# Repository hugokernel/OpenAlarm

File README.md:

OpenAlarm
=========

Un système d'alarme libre.

Caractéristiques :

- Uniquement basé sur des briques libres (OpenSource / OpenHardware)
- Autonomie très grande des modules capteurs, appelés « Node » (plusieurs mois)
- Les Node sont basés sur un µcontrolleur Atmel AVR ATMega32U4 et l'interface radio, sur un RFM12B (basé sur un Si4421 http://www.silabs.com/products/wireless/EZRadio/Pages/Si442021.aspx)
- Programmation et recharge simple des Node par USB (port µUSB inclu)
- Pas besoin de base : 2 Node suffisent à faire fonctionner une surveillance
- Possibilité de modifier les paramètres d'un Node à distance
- Technos utilisées : Arduino (Ino) pour les Node, et Python pour l'interface avec un PC
- Les entrées / sorties sont facilement accessible (au pas de 2.54mm)
- 2 leds (vertes et rouges) inclues sur chaque Node

Les premiers Node sont fonctionnel en version 1.5.0, les schémas de principe et PCB sont disponible en PDF dans le dossier https://github.com/hugokernel/OpenAlarm/blob/master/hardware/export/pdf/node/1.5.0/

Pour rester informer, ça se passe sur le site officiel d'OpenAlarm http://openalarm.net/, vous pouvez venir en parler sur le canal irc #madeinfr sur le réseau freenode.

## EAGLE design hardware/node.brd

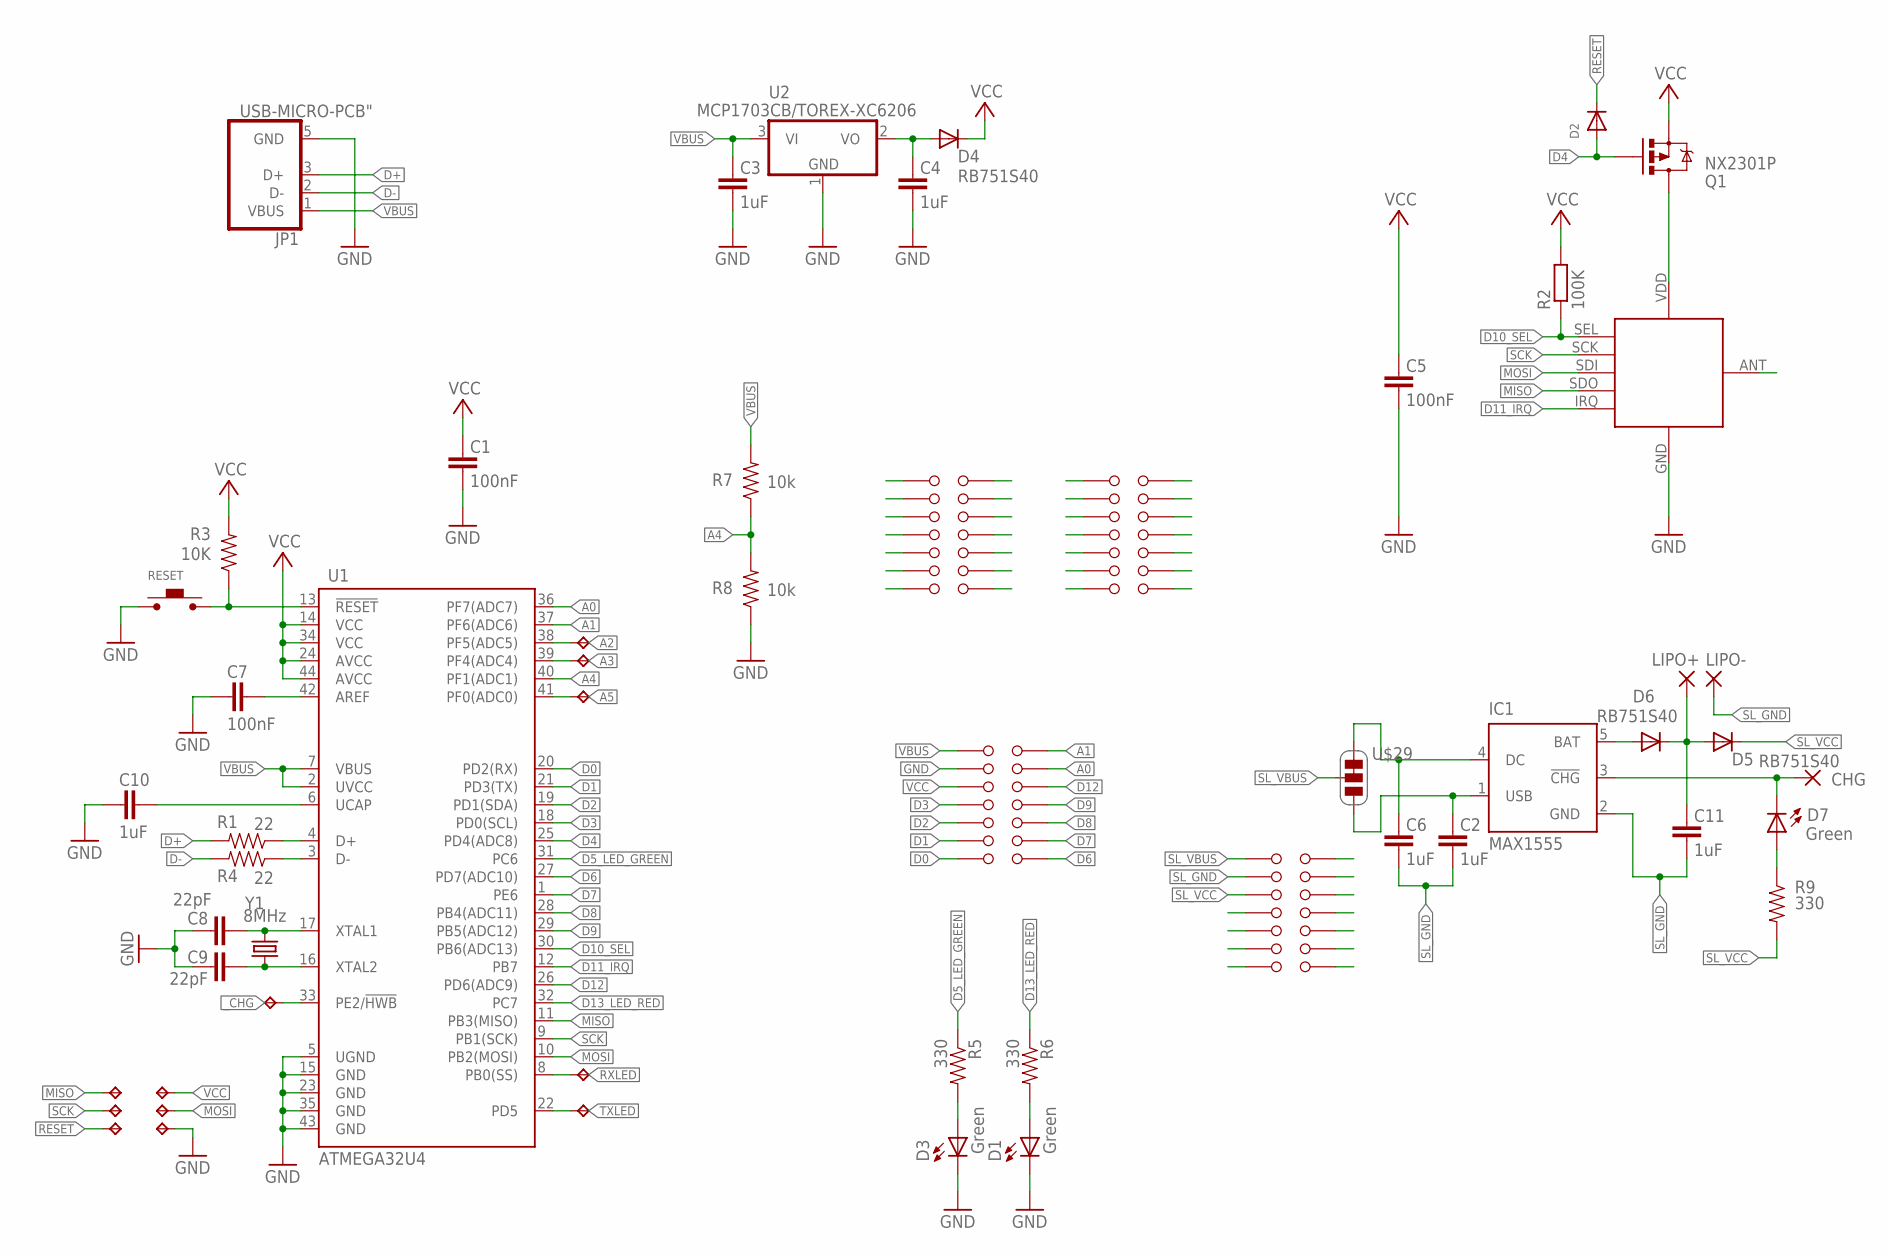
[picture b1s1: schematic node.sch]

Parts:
C1, C5, C7: 100nF; 0402-CAP
C2, C3, C4, C6, C10, C11: 1uF; 0402-CAP
C8, C9: 22pF; 0402-CAP
CHG: WIREPAD1,6/0,8; 1,6/0,8
D1, D3, D7: Green; LED-0603
D2: DIODESOD-323F; SOD-323F
D4, D5, D6: RB751S40; SOD523
IC1: MAX1555; SOT23-5L
JP1: USB-MICRO-PCB"; USB-MICRO-PCB
LIPO+: WIREPAD1,6/0,8; 1,6/0,8
LIPO-: WIREPAD1,6/0,8; 1,6/0,8
Q1: NX2301P; SOT23
R1, R4: 22; 0402-RES
R2: 100K; R0402
R3: 10K; 0402-RES
R5, R6, R9: 330; 0402-RES
R7, R8: 10k; 0402-RES
RESET: MICROSWITCH
RFMXX: RFM12B_MINPADS; RFM12B-MINPADS
TP1, TP2, TP3, TP4, TP5, TP14: TPTP13R; TP13R
TP7, TP8, TP9, TP10, TP11, TP12: TPTP08R; TP08R
U1: ATMEGA32U4; QFN-44-NOPAD
U2: MCP1703CB/TOREX-XC6206; SOT23
U$1, U$2, U$3, U$4, U$5, U$6, U$7, U$8, U$9, U$10, U$11, U$12, U$13, U$14, U$15, U$16, U$17, U$18, U$19, U$20, U$21, U$22, U$23, U$24, U$25, U$26, U$27, U$28, U$30, U$31, U$32, U$33, U$34, U$35, U$36, U$37, U$38, U$39, U$40, U$41, U$42, U$43, U$44, U$45, U$46, U$47, U$48, U$49, U$50, U$51, U$52, U$53, U$54, U$55, U$56, U$57: IOPAD
U$29: UJUMPER-SHORT
Y1: 8MHz; CRYSTAL-SMD-5X3

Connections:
A0: U1.36 (PF7(ADC7)), U$9.P$1
A1: U1.37 (PF6(ADC6)), U$8.P$1
A2: TP7.TP, U1.38 (PF5(ADC5))
A3: TP8.TP, U1.39 (PF4(ADC4))
A4: R7.1, R8.2, U1.40 (PF1(ADC1))
A5: TP10.TP, U1.41 (PF0(ADC0))
AREF: C7.2, U1.42 (AREF)
D0: U1.20 (PD2(RX)), U$2.P$1
D1: U1.21 (PD3(TX)), U$1.P$1
D2: U1.19 (PD1(SDA)), U$3.P$1
D3: U1.18 (PD0(SCL)), U$4.P$1
D4: D2.A, Q1.1 (G), U1.25 (PD4(ADC8))
D5_LED_GREEN: R5.1, U1.31 (PC6)
D6: U1.27 (PD7(ADC10)), U$14.P$1
D7: U1.1 (PE6), U$13.P$1
D8: U1.28 (PB4(ADC11)), U$12.P$1
D9: U1.29 (PB5(ADC12)), U$11.P$1
D10_SEL: R2.1, RFMXX.SEL, U1.30 (PB6(ADC13))
D11_IRQ: RFMXX.IRQ, U1.12 (PB7)
D12: U1.26 (PD6(ADC9)), U$10.P$1
D13_LED_RED: R6.1, U1.32 (PC7)
D+: JP1.3 (D+), R1.2
D-: JP1.2 (D-), R4.2
GND: C1.1, C3.1, C4.1, C5.1, C7.1, C8.2, C9.2, C10.1, D1.C, D3.C, JP1.5 (GND), R8.1, RESET.P$1, RFMXX.GND, TP5.TP, U1.5 (UGND), U1.15 (GND), U1.23 (GND), U1.35 (GND), U1.43 (GND), U2.1 (GND), U$6.P$1
MISO: RFMXX.SDO (SDO/MISO), TP14.TP, U1.11 (PB3(MISO))
MOSI: RFMXX.SDI (SDI/MOSI), TP4.TP, U1.10 (PB2(MOSI))
unnamed: C9.1, U1.16 (XTAL2), Y1.1
unnamed: R1.1, U1.4 (D+)
unnamed: C8.1, U1.17 (XTAL1), Y1.3 (2)
unnamed: C10.2, U1.6 (UCAP)
unnamed: D1.A, R6.2
unnamed: R4.1, U1.3 (D-)
unnamed: D3.A, R5.2
unnamed: Q1.3 (D), RFMXX.VDD
unnamed: D7.A, R9.1
unnamed: CHG.1, D7.C, IC1.3 (!CHG)
unnamed: C6.2, IC1.4 (DC), U$29.C0
unnamed: C2.2, IC1.1 (USB), U$29.C1
unnamed: D6.A, IC1.5 (BAT)
unnamed: C11.2, D5.A, D6.C, LIPO+.1
RESET: D2.C, R3.1, RESET.P$2, TP3.TP, U1.13 (!RESET)
RXLED: TP11.TP, U1.8 (PB0(SS))
SCK: RFMXX.SCK, TP2.TP, U1.9 (PB1(SCK))
SL_GND: C2.1, C6.1, C11.1, IC1.2 (GND), LIPO-.1, U$31.P$1
SL_VBUS: U$29.COM, U$30.P$1
SL_VCC: D5.C, R9.2, U$32.P$1
TXLED: TP9.TP, U1.22 (PD5)
VBAT: C4.2, D4.A, U2.2 (VO)
VBUS: C3.2, JP1.1 (VBUS), R7.2, U1.2 (UVCC), U1.7 (VBUS), U2.3 (VI), U$7.P$1
VCC: C1.2, C5.2, D4.C, Q1.2 (S), R2.2, R3.2, TP1.TP, U1.14 (VCC), U1.24 (AVCC), U1.34 (VCC), U1.44 (AVCC), U$5.P$1
_CHG: TP12.TP, U1.33 (PE2/!HWB)

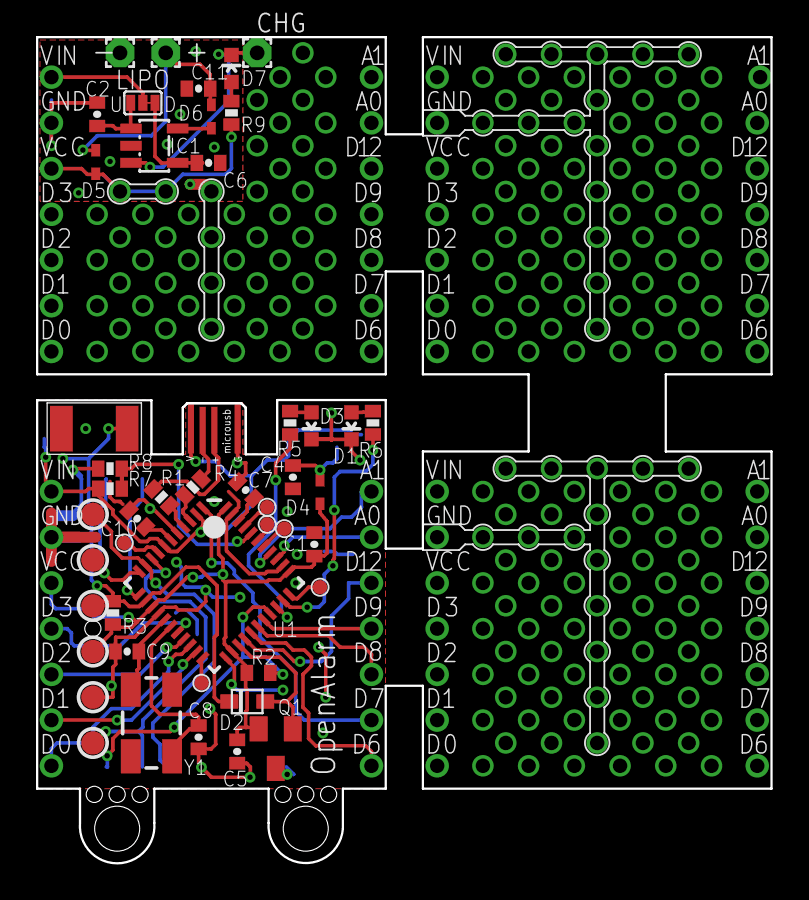
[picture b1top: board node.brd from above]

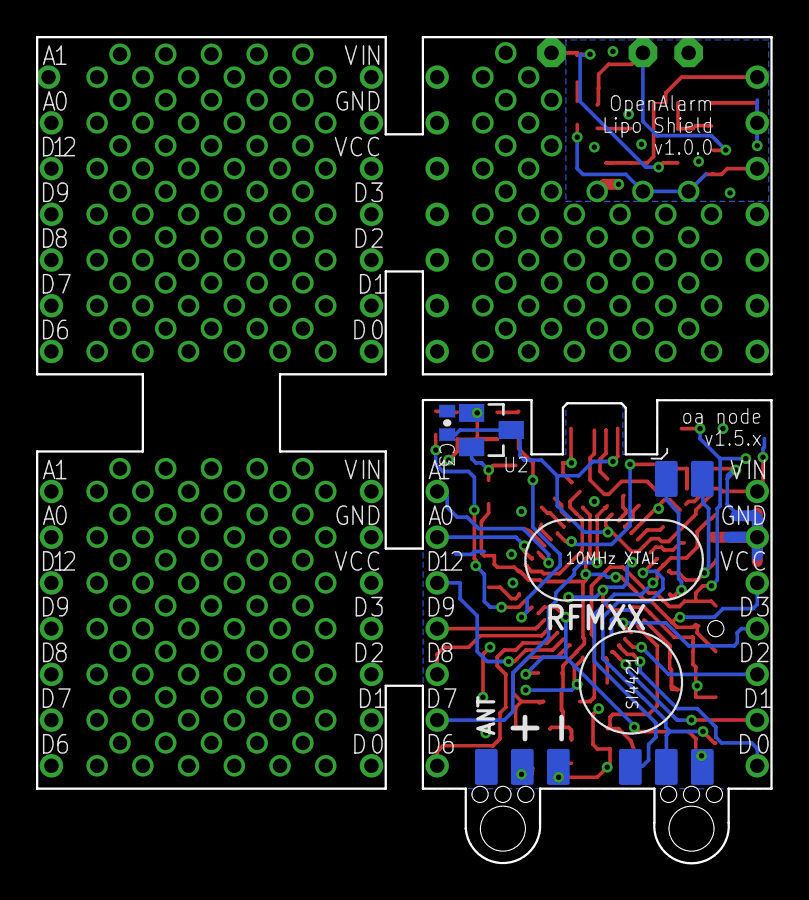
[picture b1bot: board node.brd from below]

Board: 2 copper layers, 40.8 x 45.9 mm, 107 parts (3 on the bottom side), 51 nets.

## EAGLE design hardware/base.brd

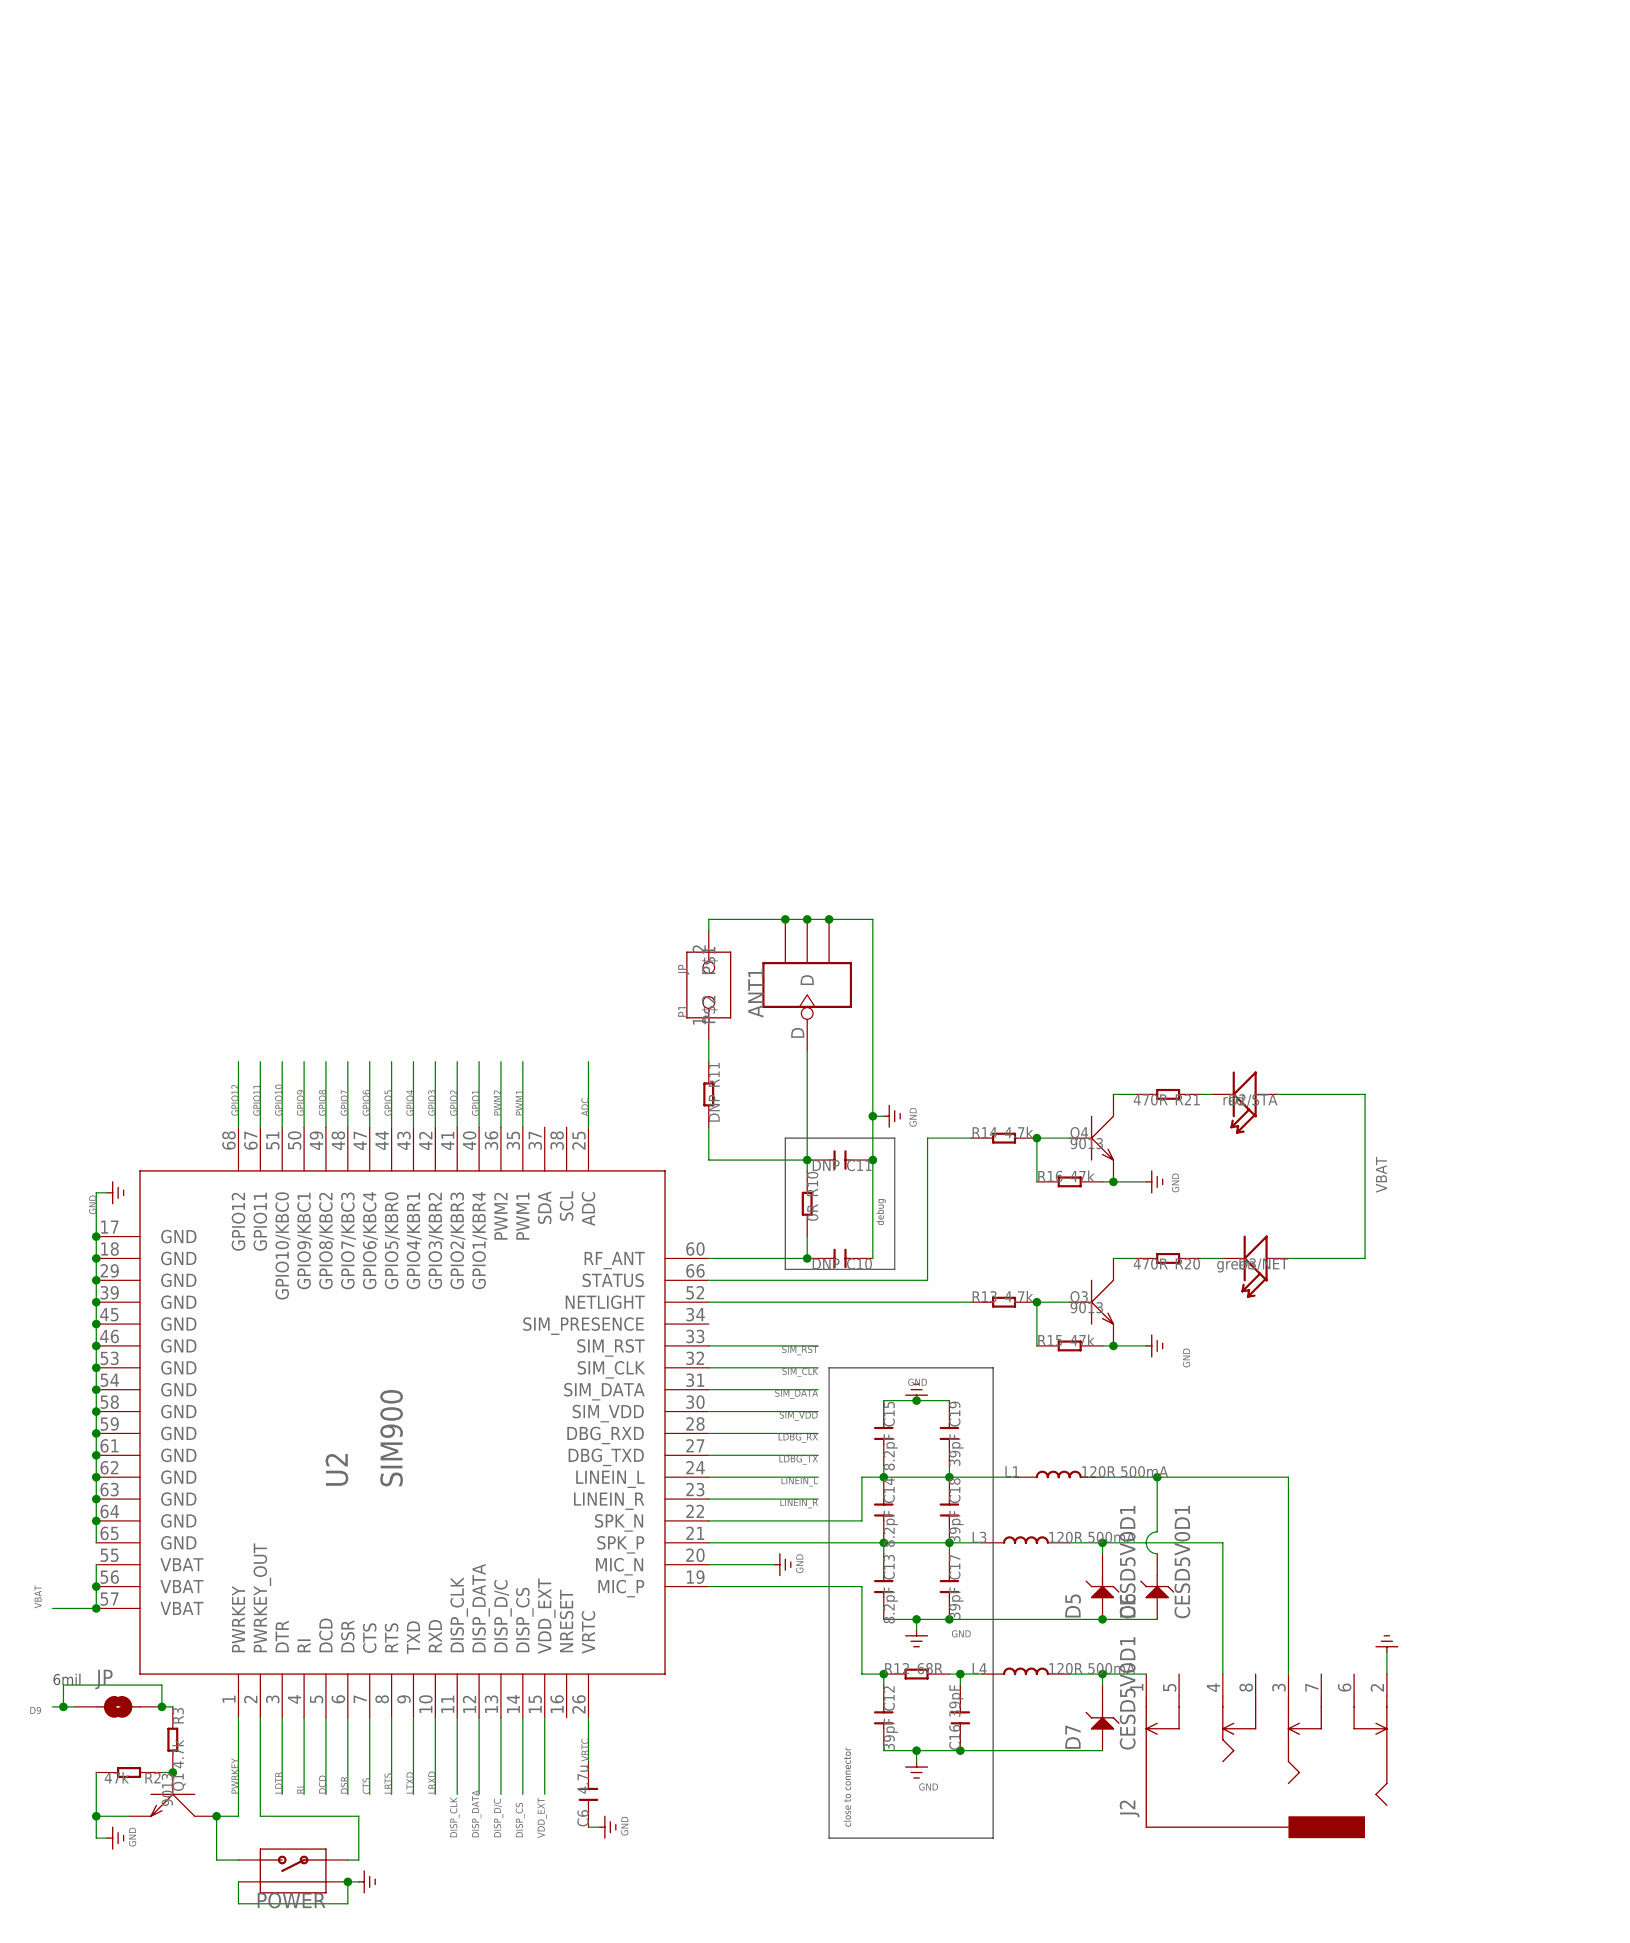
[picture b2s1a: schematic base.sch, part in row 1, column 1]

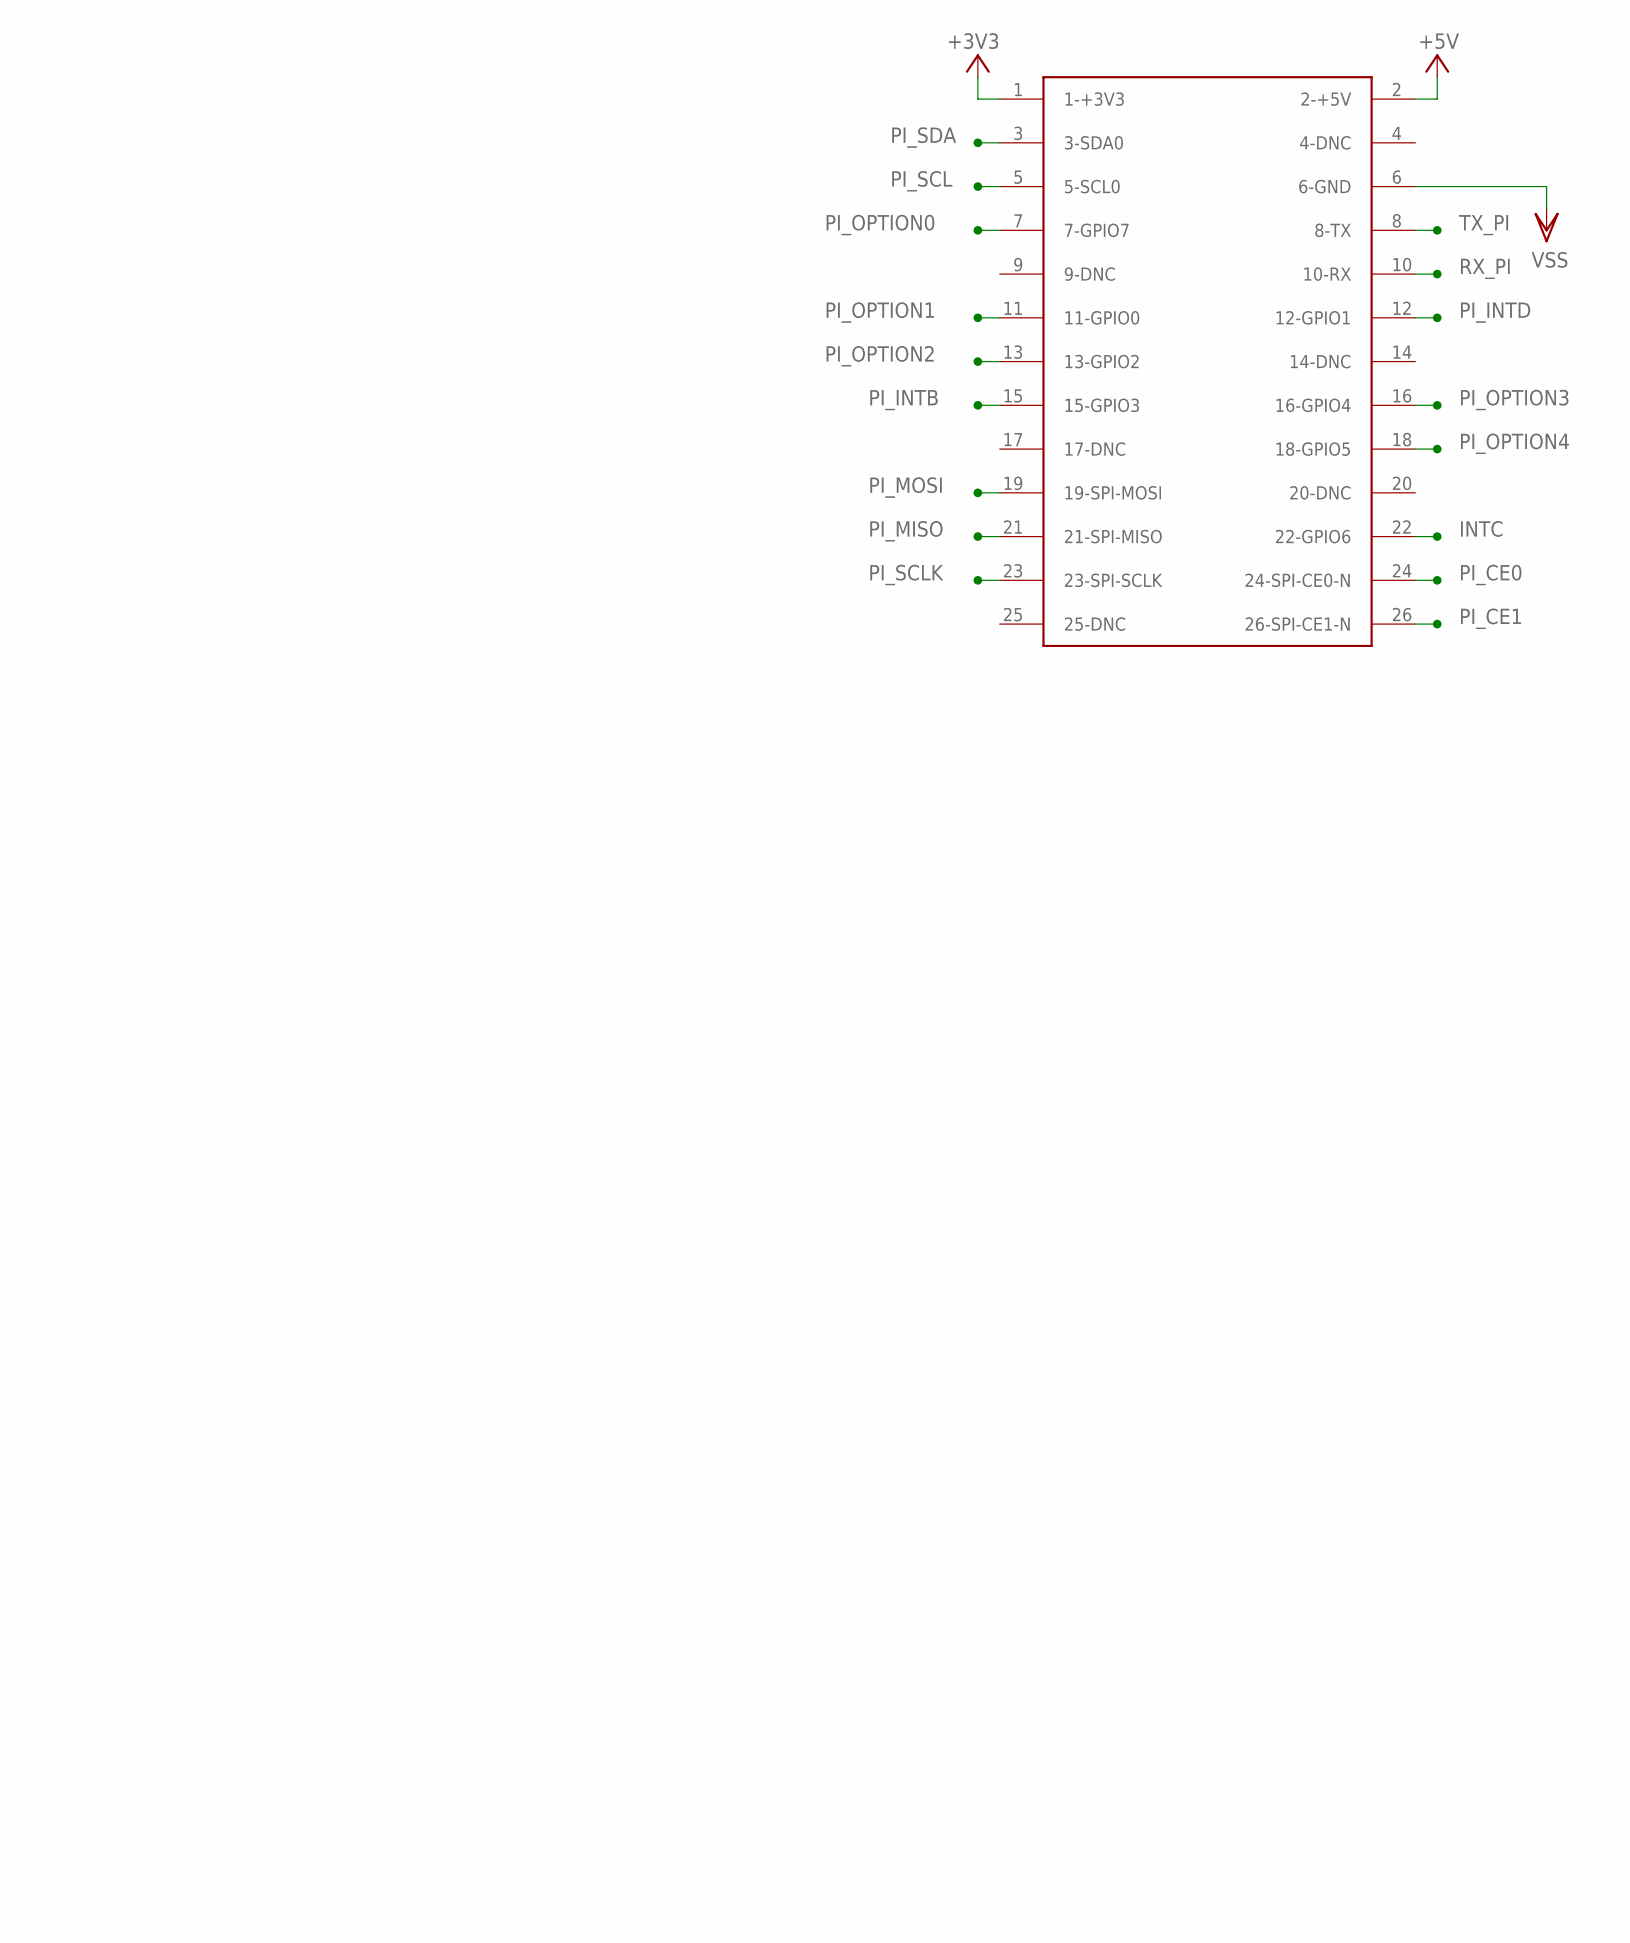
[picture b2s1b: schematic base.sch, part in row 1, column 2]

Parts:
ANT1: ANTENNA-U-FL; 4P-U-FL
C6: 4.7u; C0805
C10, C11: DNP; C0603
C12, C16, C17, C18, C19: 39pF; C0603
C13, C14, C15: 8.2pF; C0603
D2/STA: red; LED-0603
D3/NET: green; LED-0603
D5, D6, D7: CESD5V0D1; SOD123-2.7X1.6
J2: AUDIO-8P'PJ-3536-L6S'; 8P-3.5-SMD
JP: PAD-SOLDERJUMPERNC; 2P-SMD-3.3X2
L1, L3, L4: 120R 500mA; L0603
P1: JP
POWER: BUTTON-4P-REINFORCE'TS-118E'; 4P-SMD-7X3.5X3.5H
Q1, Q3, Q4: 9013; SOT23
R2, R15, R16: 47k; R0603
R3, R13, R14: 4.7k; R0603
R10: 0R; R0603
R11: DNP; R0603
R12: 68R; R0603
R20, R21: 470R; R0603
U2: SIM900
U$3: RASPBERRY-PILIGHT-HOLE; RASPBERRY-PI-LIGHT-HOLE

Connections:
+3V3: U$3.1 (1-+3V3)
+5V: U$3.2 (2-+5V)
ADC: U2.25 (ADC)
CTS: U2.7 (CTS)
D9: JP.1, JP.2, R3.1
DCD: U2.5 (DCD)
DISP_CLK: U2.11 (DISP_CLK)
DISP_CS: U2.14 (DISP_CS)
DISP_D/C: U2.13 (DISP_D/C)
DISP_DATA: U2.12 (DISP_DATA)
DSR: U2.6 (DSR)
GND: ANT1.GND1, ANT1.GND2, ANT1.GND3, C6.1, C10.1, C11.1, C12.2, C13.2, C15.1, C16.1, C17.2, C19.1, D5.1, D6.1, D7.1, J2.2, P1.2, POWER.S1, POWER.S2, Q1.2 (E), Q3.2 (E), Q4.2 (E), R2.2, R15.2, R16.2, U2.17 (GND), U2.18 (GND), U2.20 (MIC_N), U2.29 (GND), U2.39 (GND), U2.45 (GND), U2.46 (GND), U2.53 (GND), U2.54 (GND), U2.58 (GND), U2.59 (GND), U2.61 (GND), U2.62 (GND), U2.63 (GND), U2.64 (GND), U2.65 (GND)
GPIO1: U2.40 (GPIO1/KBR4)
GPIO2: U2.41 (GPIO2/KBR3)
GPIO3: U2.42 (GPIO3/KBR2)
GPIO4: U2.43 (GPIO4/KBR1)
GPIO5: U2.44 (GPIO5/KBR0)
GPIO6: U2.47 (GPIO6/KBC4)
GPIO7: U2.48 (GPIO7/KBC3)
GPIO8: U2.49 (GPIO8/KBC2)
GPIO9: U2.50 (GPIO9/KBC1)
GPIO10: U2.51 (GPIO10/KBC0)
GPIO11: U2.67 (GPIO11)
GPIO12: U2.68 (GPIO12)
INTC: U$3.22 (22-GPIO6)
LDBG_RX: U2.28 (DBG_RXD)
LDBG_TX: U2.27 (DBG_TXD)
LDTR: U2.3 (DTR)
LINEIN_L: U2.24 (LINEIN_L)
LINEIN_R: U2.23 (LINEIN_R)
LRTS: U2.8 (RTS)
LRXD: U2.10 (RXD)
LTXD: U2.9 (TXD)
unnamed: D2/STA.-, R21.1
unnamed: C10.2, R10.2, U2.60 (RF_ANT)
unnamed: Q3.3 (C), R20.2
unnamed: D3/NET.-, R20.1
unnamed: Q3.1 (B), R13.2, R15.1
unnamed: R13.1, U2.52 (NETLIGHT)
unnamed: POWER.1, U2.2 (PWRKEY_OUT)
unnamed: C12.1, R12.1, U2.19 (MIC_P)
unnamed: C13.1, C14.2, C17.1, C18.2, L3.1, U2.21 (SPK_P)
unnamed: Q4.3 (C), R21.2
unnamed: Q4.1 (B), R14.2, R16.1
unnamed: C14.1, C15.2, C18.1, C19.2, L1.1, U2.22 (SPK_N)
unnamed: R14.1, U2.66 (STATUS)
unnamed: ANT1.D, C11.2, R10.1, R11.2
unnamed: C16.2, L4.1, R12.2
unnamed: Q1.1 (B), R2.1, R3.2
unnamed: D7.2, J2.1, L4.2
unnamed: D5.2, J2.4, L3.2
unnamed: D6.2, J2.3, L1.2
unnamed: P1.1, R11.1
PI_CE0: U$3.24 (24-SPI-CE0-N)
PI_CE1: U$3.26 (26-SPI-CE1-N)
PI_INTB: U$3.15 (15-GPIO3)
PI_INTD: U$3.12 (12-GPIO1)
PI_MISO: U$3.21 (21-SPI-MISO)
PI_MOSI: U$3.19 (19-SPI-MOSI)
PI_OPTION0: U$3.7 (7-GPIO7)
PI_OPTION1: U$3.11 (11-GPIO0)
PI_OPTION2: U$3.13 (13-GPIO2)
PI_OPTION3: U$3.16 (16-GPIO4)
PI_OPTION4: U$3.18 (18-GPIO5)
PI_SCL: U$3.5 (5-SCL0)
PI_SCLK: U$3.23 (23-SPI-SCLK)
PI_SDA: U$3.3 (3-SDA0)
PWM1: U2.35 (PWM1)
PWM2: U2.36 (PWM2)
PWRKEY: POWER.2, Q1.3 (C), U2.1 (PWRKEY)
RI: U2.4 (RI)
RX_PI: U$3.10 (10-RX)
SIM_CLK: U2.32 (SIM_CLK)
SIM_DATA: U2.31 (SIM_DATA)
SIM_RST: U2.33 (SIM_RST)
SIM_VDD: U2.30 (SIM_VDD)
TX_PI: U$3.8 (8-TX)
VBAT: D2/STA.+, D3/NET.+, U2.55 (VBAT), U2.56 (VBAT), U2.57 (VBAT)
VDD_EXT: U2.15 (VDD_EXT)
VRTC: C6.2, U2.26 (VRTC)
VSS: U$3.6 (6-GND)

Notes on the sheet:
close to connector
debug
6mil

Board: 2 copper layers, 42 parts (1 on the bottom side), 25 nets, no tracks yet.

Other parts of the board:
U$2: OSHW_8X350_NOTEXT
U$5: OSHW_6X150_NOTEXT

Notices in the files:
parts and their libraries:
SparkFun: Licensing: CC v3.0 Share-Alike You are welcome to use this library for commercial purposes.
